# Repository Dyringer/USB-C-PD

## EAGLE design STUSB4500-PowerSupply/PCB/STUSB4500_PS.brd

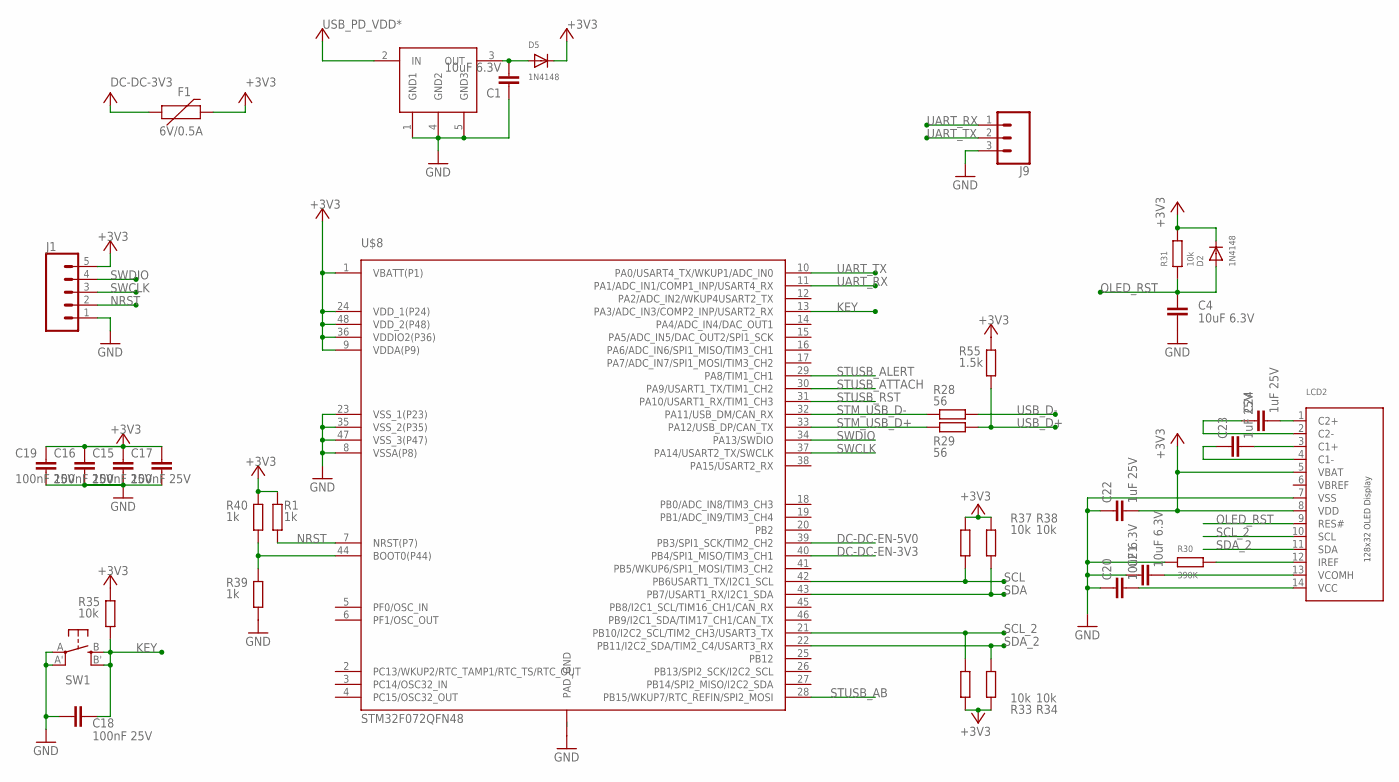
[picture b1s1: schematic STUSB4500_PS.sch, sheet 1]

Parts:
C1, C4, C20, C21: 10uF 6.3V; C0603
C15, C16, C17, C18, C19: 100nF 25V; C0402
C22, C23, C24: 1uF 25V; C0603
D2, D5: 1N4148; SOD-323F
F1: 6V/0.5A; 1206
J1: CONN_05LOCK; 1X05_LOCK
J9: CONN_03LOCK_NO_SILK; 1X03_LOCK_NO_SILK
LCD2: DISP_OLED_UG-2832HSWEG02; UG-2832HSWEG02_WRAPUNDER
R1, R39, R40: 1k; R0402
R28, R29: 56; R0402
R30: 390K; R0603
R31: 10k; R0603
R33, R34, R35, R37, R38: 10k; R0402
R55: 1.5k; R0402
SW1: SPST_TACT-EVQQ2; EVQ-Q2
U$1: TLV704_3V3SOT23-5; SOT23-5
U$8: STM32F072QFN48; P-HVQFN48-7X7

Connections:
+3V3: C15.1, C16.1, C17.1, C19.1, C22.2, D2.C, D5.C, F1.2, J1.5, LCD2.5 (VBAT), LCD2.8 (VDD), R1.2, R31.2, R33.2, R34.2, R35.2, R37.2, R38.2, R40.2, R55.2, U$8.1 (VBATT(P1)), U$8.9 (VDDA(P9)), U$8.24 (VDD_1(P24)), U$8.36 (VDDIO2(P36)), U$8.48 (VDD_2(P48)); also elsewhere on the board
DC-DC-3V3: F1.1; also elsewhere on the board
DC-DC-EN-3V3: U$8.40 (PB4/SPI1_MISO/TIM3_CH1); also elsewhere on the board
DC-DC-EN-5V0: U$8.39 (PB3/SPI1_SCK/TIM2_CH2); also elsewhere on the board
GND: C1.1, C4.1, C15.2, C16.2, C17.2, C18.1, C19.2, C20.1, C21.1, C22.1, J1.1, J9.3, LCD2.7 (VSS), R30.1, R39.1, SW1.A, SW1.A' (P1), U$1.1 (GND1), U$1.4 (GND2), U$1.5 (GND3), U$8.8 (VSSA(P8)), U$8.23 (VSS_1(P23)), U$8.35 (VSS_2(P35)), U$8.47 (VSS_3(P47)), U$8._ (PAD_GND); also elsewhere on the board
KEY: C18.2, R35.1, SW1.B (S), SW1.B' (S1), U$8.13 (PA3/ADC_IN3/COMP2_INP/USART2_RX)
unnamed: C1.2, D5.A, U$1.3 (OUT)
unnamed: R39.2, R40.1, U$8.44 (BOOT0(P44))
unnamed: C24.2, LCD2.1 (C2+)
unnamed: C24.1, LCD2.2 (C2-)
unnamed: C23.2, LCD2.3 (C1+)
unnamed: C23.1, LCD2.4 (C1-)
unnamed: C21.2, LCD2.13 (VCOMH)
unnamed: LCD2.12 (IREF), R30.2
unnamed: C20.2, LCD2.14 (VCC)
NRST: J1.2, R1.1, U$8.7 (NRST(P7))
OLED_RST: C4.2, D2.A, LCD2.9 (RES#), R31.1
SCL: R37.1, U$8.42 (PB6USART1_TX/I2C1_SCL); also elsewhere on the board
SCL_2: LCD2.10 (SCL), R33.1, U$8.21 (PB10/I2C2_SCL/TIM2_CH3/USART3_TX); also elsewhere on the board
SDA: R38.1, U$8.43 (PB7/USART1_RX/I2C1_SDA); also elsewhere on the board
SDA_2: LCD2.11 (SDA), R34.1, U$8.22 (PB11/I2C2_SDA/TIM2_C4/USART3_RX); also elsewhere on the board
STM_USB_D+: R29.1, U$8.33 (PA12/USB_DP/CAN_TX)
STM_USB_D-: R28.1, U$8.32 (PA11/USB_DM/CAN_RX)
STUSB_AB: U$8.28 (PB15/WKUP7/RTC_REFIN/SPI2_MOSI); also elsewhere on the board
STUSB_ALERT: U$8.29 (PA8/TIM1_CH1); also elsewhere on the board
STUSB_ATTACH: U$8.30 (PA9/USART1_TX/TIM1_CH2); also elsewhere on the board
STUSB_RST: U$8.31 (PA10/USART1_RX/TIM1_CH3); also elsewhere on the board
SWCLK: J1.3, U$8.37 (PA14/USART2_TX/SWCLK)
SWDIO: J1.4, U$8.34 (PA13/SWDIO)
UART_RX: J9.1, U$8.11 (PA1/ADC_IN1/COMP1_INP/USART4_RX)
UART_TX: J9.2, U$8.10 (PA0/USART4_TX/WKUP1/ADC_IN0)
USB_D+: R29.2, R55.1; also elsewhere on the board
USB_D-: R28.2; also elsewhere on the board
USB_PD_VDD*: U$1.2 (IN); also elsewhere on the board
VBREF: LCD2.6 (VBREF)

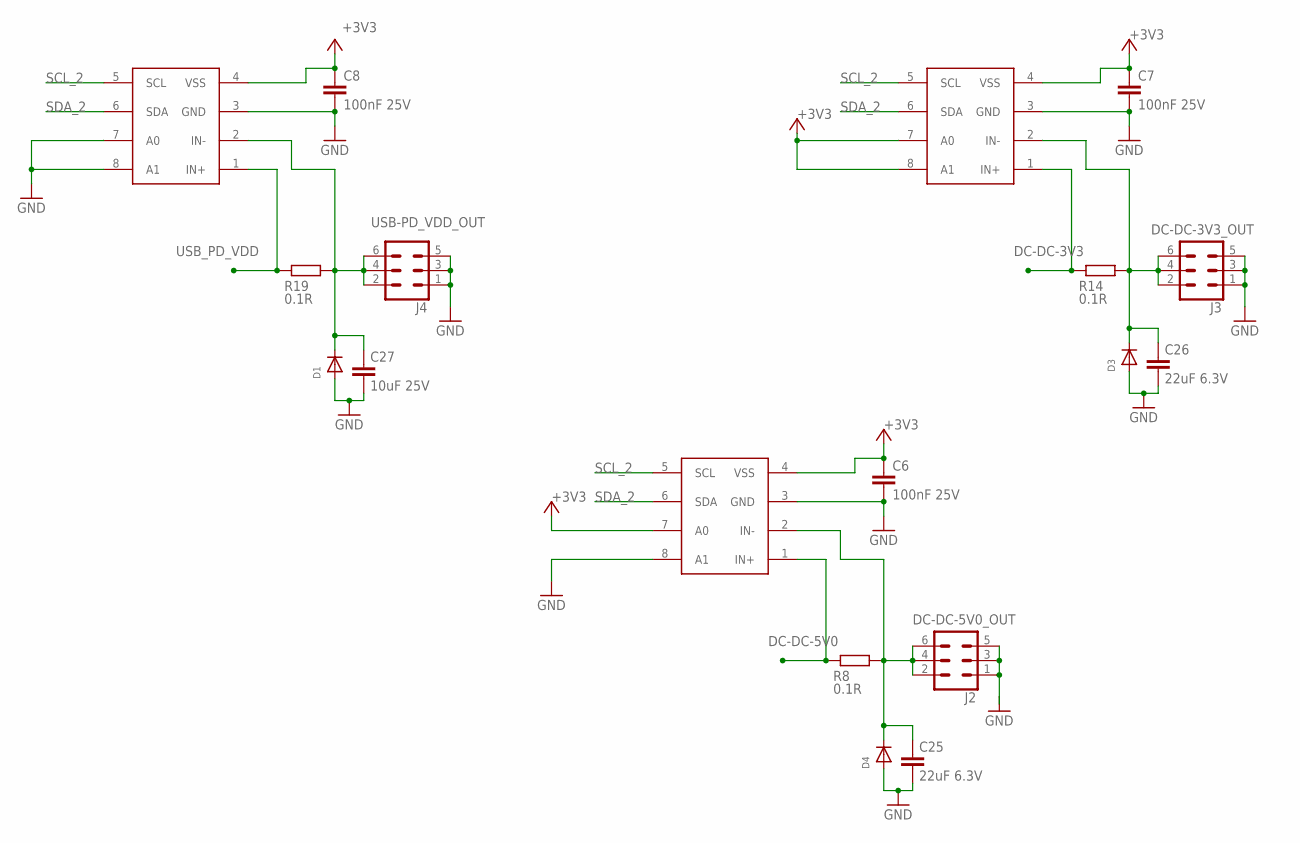
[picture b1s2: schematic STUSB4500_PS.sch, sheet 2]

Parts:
C6, C7, C8: 100nF 25V; C0402
C25, C26: 22uF 6.3V; C1206
C27: 10uF 25V; C1206
D1, D3, D4: DIODE_SOD-123FL; SOD-123FL
J2, J3, J4: FEMALE 2x3; 2X3-NS
R8, R14, R19: 0.1R; R2010
U$7, U$9, U$10: INA219DCN; DCN-R-PDSO-G8

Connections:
+3V3: C6.1, C7.1, C8.1, U$7.4 (VSS), U$7.7 (A0), U$9.4 (VSS), U$9.7 (A0), U$9.8 (A1), U$10.4 (VSS); also elsewhere on the board
DC-DC-3V3: R14.2, U$9.1 (IN+); also elsewhere on the board
DC-DC-3V3_OUT: C26.1, D3.C, J3.2, J3.4, J3.6, R14.1, U$9.2 (IN-)
DC-DC-5V0: R8.2, U$7.1 (IN+); also elsewhere on the board
DC-DC-5V0_OUT: C25.1, D4.C, J2.2, J2.4, J2.6, R8.1, U$7.2 (IN-)
GND: C6.2, C7.2, C8.2, C25.2, C26.2, C27.2, D1.A, D3.A, D4.A, J2.1, J2.3, J2.5, J3.1, J3.3, J3.5, J4.1, J4.3, J4.5, U$7.3 (GND), U$7.8 (A1), U$9.3 (GND), U$10.3 (GND), U$10.7 (A0), U$10.8 (A1); also elsewhere on the board
SCL_2: U$7.5 (SCL), U$9.5 (SCL), U$10.5 (SCL); also elsewhere on the board
SDA_2: U$7.6 (SDA), U$9.6 (SDA), U$10.6 (SDA); also elsewhere on the board
USB-PD_VDD_OUT: C27.1, D1.C, J4.2, J4.4, J4.6, R19.1, U$10.2 (IN-)
USB_PD_VDD: R19.2, U$10.1 (IN+); also elsewhere on the board

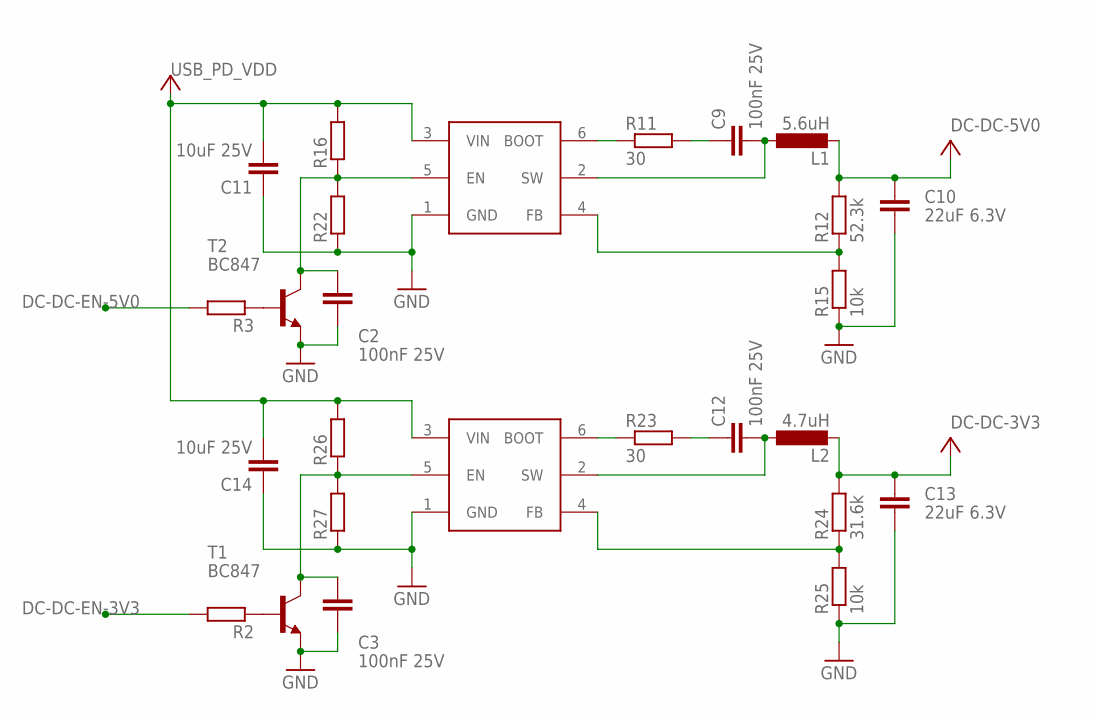
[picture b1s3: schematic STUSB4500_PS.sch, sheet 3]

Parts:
C2, C3, C9, C12: 100nF 25V; C0402
C10, C13: 22uF 6.3V; C1206
C11, C14: 10uF 25V; C1206
L1: 5.6uH; POWER-CHOKE_WE-TPC
L2: 4.7uH; POWER-CHOKE_WE-TPC
R2, R3, R16, R22, R26, R27: R-EU_R0402; R0402
R11, R23: 30; R0402
R12: 52.3k; R0603
R15, R25: 10k; R0603
R24: 31.6k; R0603
T1, T2: BC847; SOT23
U$11, U$12: TPS56339SOT23-6; TEXAS_SOT23-6

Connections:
DC-DC-3V3: C13.2, L2.2, R24.2; also elsewhere on the board
DC-DC-5V0: C10.2, L1.2, R12.2; also elsewhere on the board
DC-DC-EN-3V3: R2.2; also elsewhere on the board
DC-DC-EN-5V0: R3.2; also elsewhere on the board
GND: C2.1, C3.1, C10.1, C11.1, C13.1, C14.1, R15.1, R22.1, R25.1, R27.1, T1.2 (E), T2.2 (E), U$11.1 (GND), U$12.1 (GND); also elsewhere on the board
unnamed: R2.1, T1.1 (B)
unnamed: R3.1, T2.1 (B)
unnamed: R12.1, R15.2, U$11.4 (FB)
unnamed: C2.2, R16.1, R22.2, T2.3 (C), U$11.5 (EN)
unnamed: R24.1, R25.2, U$12.4 (FB)
unnamed: R11.1, U$11.6 (BOOT)
unnamed: C9.1, R11.2
unnamed: C3.2, R26.1, R27.2, T1.3 (C), U$12.5 (EN)
unnamed: C9.2, L1.1, U$11.2 (SW)
unnamed: R23.1, U$12.6 (BOOT)
unnamed: C12.1, R23.2
unnamed: C12.2, L2.1, U$12.2 (SW)
USB_PD_VDD: C11.2, C14.2, R16.2, R26.2, U$11.3 (VIN), U$12.3 (VIN); also elsewhere on the board

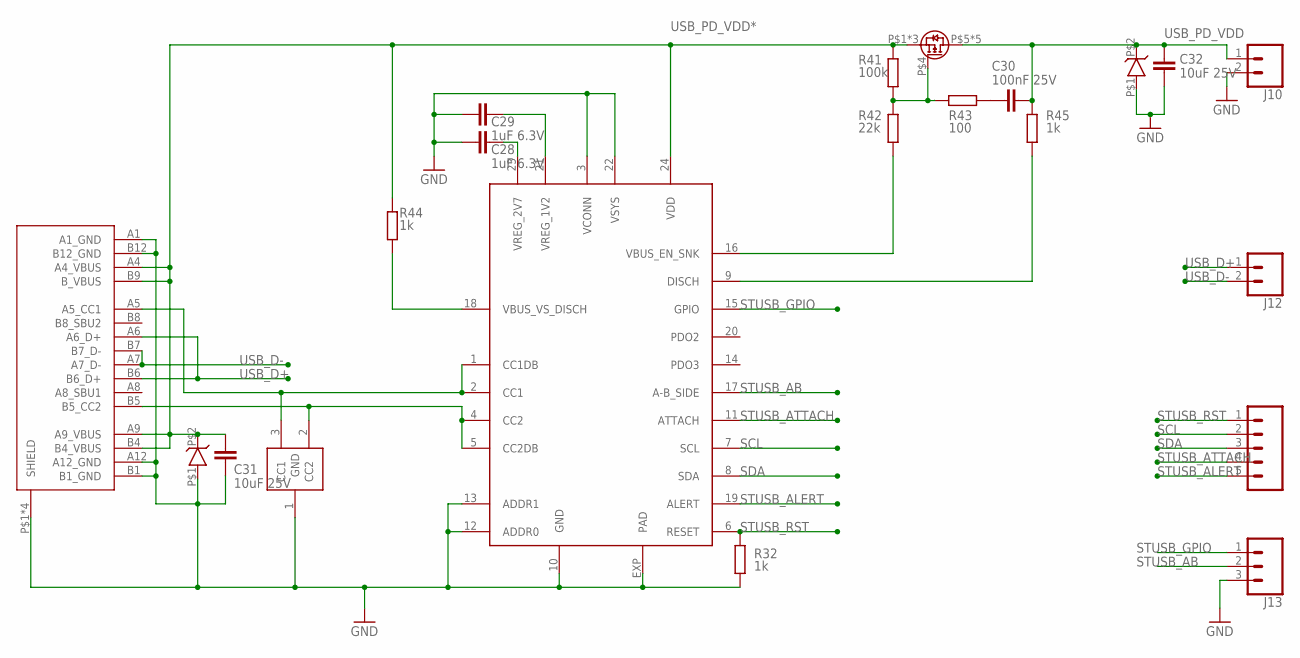
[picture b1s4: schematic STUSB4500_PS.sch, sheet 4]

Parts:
C28, C29: 1uF 6.3V; C0402
C30: 100nF 25V; C0402
C31, C32: 10uF 25V; C1206
ESDA25W1: ESDA25WSOT323; SOT323
J10: CONN_02LOCK; 1X02_LOCK
J11: CONN_051.27MM; 1X05_1.27MM
J12: CONN_021.27; 1X02_1.27MM
J13: CONN_031.27; 1X03_1.27MM
R32, R44, R45: 1k; R0402
R41: 100k; R0402
R42: 22k; R0402
R43: 100; R0402
U$3: STUSB4500QFN24_4X4; QFN24-4X4
U$13: USB-C; USB-C_16P
U$14, U$15: ESDA25P35; 1610
U$16: STL6P3LLH6; POWER_FLAT_3X3

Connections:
GND: C28.2, C29.2, C31.2, C32.2, ESDA25W1.1 (GND), J10.2, J13.3, R32.1, U$3.3 (VCONN), U$3.10 (GND), U$3.12 (ADDR0), U$3.13 (ADDR1), U$3.22 (VSYS), U$3.EXP (PAD), U$13.A1 (A1_GND), U$13.A12 (A12_GND), U$13.B1 (B1_GND), U$13.B12 (B12_GND), U$13.P$1 (SHIELD), U$13.P$2 (SHIELD), U$13.P$3 (SHIELD), U$13.P$4 (SHIELD), U$14.P$1 (GND), U$15.P$1 (GND); also elsewhere on the board
unnamed: R41.1, R42.2, R43.2, U$16.P$4 (G)
unnamed: R44.2, U$3.18 (VBUS_VS_DISCH)
unnamed: ESDA25W1.3 (CC1), U$3.1 (CC1DB), U$3.2 (CC1), U$13.A5 (A5_CC1)
unnamed: ESDA25W1.2 (CC2), U$3.4 (CC2), U$3.5 (CC2DB), U$13.B5 (B5_CC2)
unnamed: R42.1, U$3.16 (VBUS_EN_SNK)
unnamed: C30.1, R43.1
unnamed: R45.2, U$3.9 (DISCH)
unnamed: C28.1, U$3.23 (VREG_2V7)
unnamed: C29.1, U$3.21 (VREG_1V2)
SCL: J11.2, U$3.7 (SCL); also elsewhere on the board
SDA: J11.3, U$3.8 (SDA); also elsewhere on the board
STUSB_AB: J13.2, U$3.17 (A-B_SIDE); also elsewhere on the board
STUSB_ALERT: J11.5, U$3.19 (ALERT); also elsewhere on the board
STUSB_ATTACH: J11.4, U$3.11 (ATTACH); also elsewhere on the board
STUSB_GPIO: J13.1, U$3.15 (GPIO)
STUSB_RST: J11.1, R32.2, U$3.6 (RESET); also elsewhere on the board
USB_D+: J12.1, U$13.A6 (A6_D+), U$13.B6 (B6_D+); also elsewhere on the board
USB_D-: J12.2, U$13.A7 (A7_D-), U$13.B7 (B7_D-); also elsewhere on the board
USB_PD_VDD: C30.2, C32.1, J10.1, R45.1, U$15.P$2 (VBUS), U$16.P$5 (D), U$16.P$6 (D), U$16.P$7 (D), U$16.P$8 (D), U$16.P$9 (D); also elsewhere on the board
USB_PD_VDD*: C31.1, R41.2, R44.1, U$3.24 (VDD), U$13.A4 (A4_VBUS), U$13.A9 (A9_VBUS), U$13.B4 (B4_VBUS), U$13.B9 (B_VBUS), U$14.P$2 (VBUS), U$16.P$1 (S), U$16.P$2 (S), U$16.P$3 (S); also elsewhere on the board

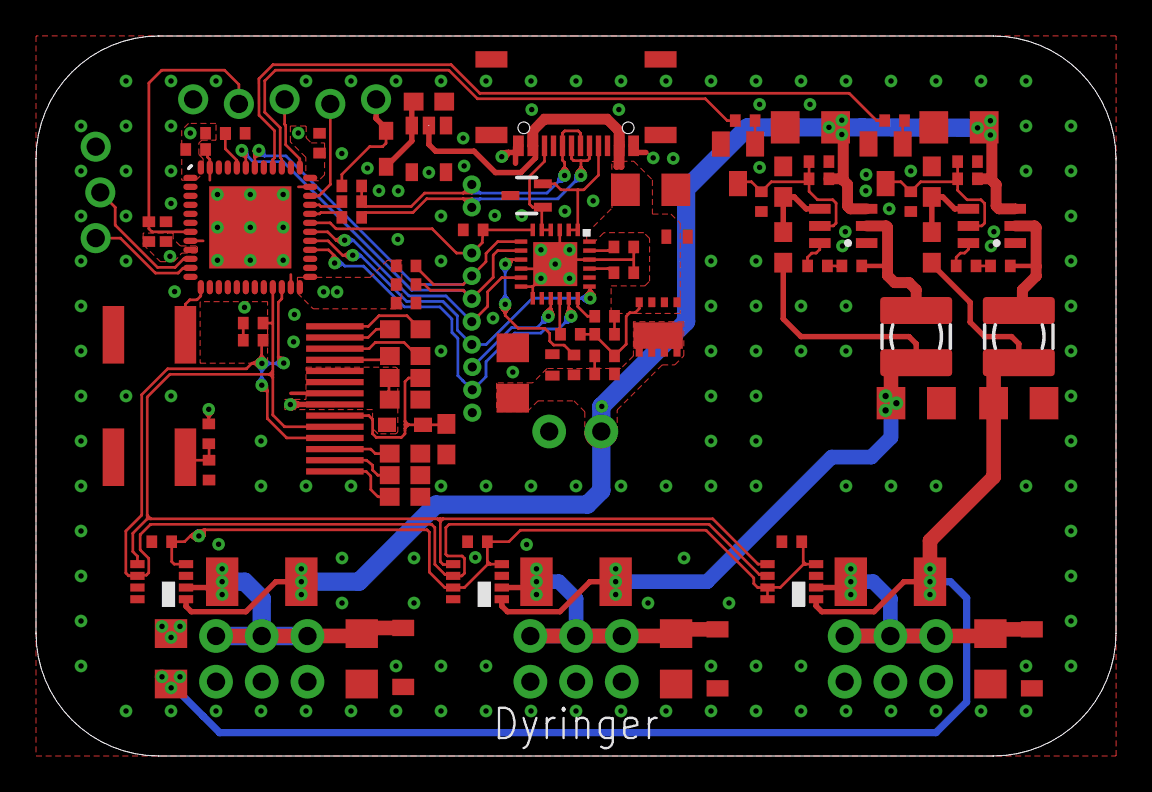
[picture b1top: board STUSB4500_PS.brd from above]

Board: 2 copper layers, 60.0 x 40.0 mm, 99 parts (0 on the bottom side), 61 nets.

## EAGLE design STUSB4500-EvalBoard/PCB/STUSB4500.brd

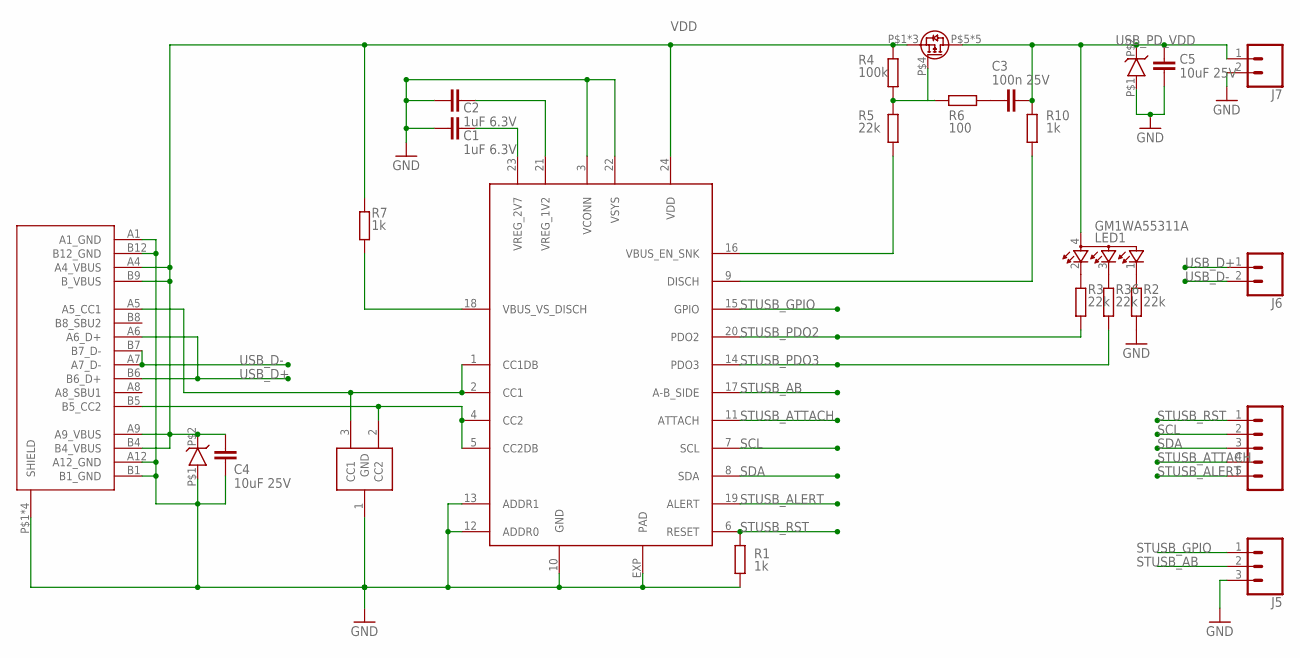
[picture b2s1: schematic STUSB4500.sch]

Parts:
C1, C2: 1uF 6.3V; C0402
C3: 100n 25V; C0402
C4, C5: 10uF 25V; C1206
ESDA25W: ESDA25WSOT323; SOT323
J5: CONN_031.27; 1X03_1.27MM
J6: CONN_021.27; 1X02_1.27MM
J7: CONN_02LOCK; 1X02_LOCK
J8: CONN_051.27MM; 1X05_1.27MM
LED1: GM1WA55311A
R1, R7, R10: 1k; R0402
R2, R3, R5, R36: 22k; R0402
R4: 100k; R0402
R6: 100; R0402
U$1: STUSB4500QFN24_4X4; QFN24-4X4
U$2: USB-C; USB-C_16P
U$4, U$5: ESDA25P35; 1610
U$6: STL6P3LLH6; POWER_FLAT_3X3

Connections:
GND: C1.2, C2.2, C4.2, C5.2, ESDA25W.1 (GND), J5.3, J7.2, R1.1, R2.1, U$1.3 (VCONN), U$1.10 (GND), U$1.12 (ADDR0), U$1.13 (ADDR1), U$1.22 (VSYS), U$1.EXP (PAD), U$2.A1 (A1_GND), U$2.A12 (A12_GND), U$2.B1 (B1_GND), U$2.B12 (B12_GND), U$2.P$1 (SHIELD), U$2.P$2 (SHIELD), U$2.P$3 (SHIELD), U$2.P$4 (SHIELD), U$4.P$1 (GND), U$5.P$1 (GND)
unnamed: LED1.1 (CGREEN), R2.2
unnamed: R4.1, R5.2, R6.2, U$6.P$4 (G)
unnamed: R7.2, U$1.18 (VBUS_VS_DISCH)
unnamed: LED1.2 (CRED), R3.2
unnamed: C3.1, R6.1
unnamed: ESDA25W.3 (CC1), U$1.1 (CC1DB), U$1.2 (CC1), U$2.A5 (A5_CC1)
unnamed: ESDA25W.2 (CC2), U$1.4 (CC2), U$1.5 (CC2DB), U$2.B5 (B5_CC2)
unnamed: R5.1, U$1.16 (VBUS_EN_SNK)
unnamed: R10.2, U$1.9 (DISCH)
unnamed: C1.1, U$1.23 (VREG_2V7)
unnamed: C2.1, U$1.21 (VREG_1V2)
unnamed: LED1.3 (CBLUE), R36.2
SCL: J8.2, U$1.7 (SCL)
SDA: J8.3, U$1.8 (SDA)
STUSB_AB: J5.2, U$1.17 (A-B_SIDE)
STUSB_ALERT: J8.5, U$1.19 (ALERT)
STUSB_ATTACH: J8.4, U$1.11 (ATTACH)
STUSB_GPIO: J5.1, U$1.15 (GPIO)
STUSB_PDO2: R3.1, U$1.20 (PDO2)
STUSB_PDO3: R36.1, U$1.14 (PDO3)
STUSB_RST: J8.1, R1.2, U$1.6 (RESET)
USB_D+: J6.1, U$2.A6 (A6_D+), U$2.B6 (B6_D+)
USB_D-: J6.2, U$2.A7 (A7_D-), U$2.B7 (B7_D-)
USB_PD_VDD: C3.2, C5.1, J7.1, LED1.4 (A), R10.1, U$5.P$2 (VBUS), U$6.P$5 (D), U$6.P$6 (D), U$6.P$7 (D), U$6.P$8 (D), U$6.P$9 (D)
VDD: C4.1, R4.2, R7.1, U$1.24 (VDD), U$2.A4 (A4_VBUS), U$2.A9 (A9_VBUS), U$2.B4 (B4_VBUS), U$2.B9 (B_VBUS), U$4.P$2 (VBUS), U$6.P$1 (S), U$6.P$2 (S), U$6.P$3 (S)

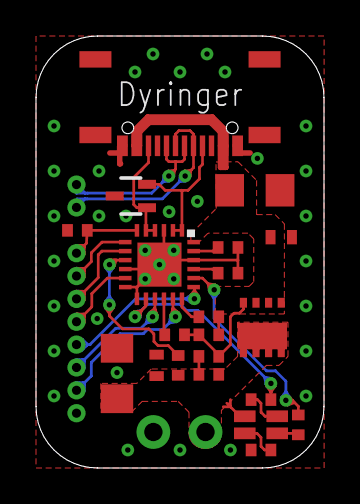
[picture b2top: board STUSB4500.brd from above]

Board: 2 copper layers, 16.0 x 24.0 mm, 25 parts (0 on the bottom side), 26 nets.

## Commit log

2019-12-27 Cleanups
2019-12-27 Fixed isolation value on top layer
2019-12-27 Fixed isolation value on top layer (#2)
2019-12-27 Initial commit - added pcb files, libs and fixed libs
2019-12-27 Removed unused libs, added todo, added missing stock libs in eval board
2019-12-28 Cleanups in stusb4500 eval
2019-12-28 UART and 3V3
2019-12-28 Added output caps and diodes
2019-12-28 Cleanups replaced button with adafruit one
2019-12-28 Unified 0402 footprint, reduced height of stusb4500 eval board to 24mm
2019-12-28 0.3mm vias
2019-12-28 Updated stusb part
2019-12-29 Cleanups in BOM, fixed OLED layout
2019-12-29 Added alternate 3V3 source
2019-12-29 Routed additional signals from stusb to stm32 removed teadrops from big pads
2019-12-29 Added reset pullup
2019-12-30 removed some unnecessary elements, added uc controlled dc-dc enable
2020-01-01 Fixed OLED design, moved some lines
2020-01-04 Changed DC-DC coils to Wurth

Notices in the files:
parts and their libraries:
DD_SparkFun-Connectors: Licensing: Creative Commons ShareAlike 4.0 International - https://creativecommons.org/licenses/by-sa/4.0
DD_microbuilder: This work is placed in the public domain, and may be freely used for commercial and non-commercial work with the following conditions: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
